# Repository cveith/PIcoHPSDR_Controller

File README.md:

# PIcoHPSDR Controller

A hardware controller for the piHPSDR application by John Melton, G0ORX.
I've called it PIcoHPSDR Controller, as it's using the newly released Raspberry Pi Pico as an abstraction layer to the hardware.

Inspired by the original controller and therefore parts of this work is based on the original PiHPSDR Controller designed by Kjell Karlsen, LA2NI, et al.
Many thanks Kjell.

## Features
- 1 VFO encoder (5V, open collector outputs)
- 4 Dual Shaft encoders (Alps EC11E type)
- 16 Push Buttons
- PTT, Up, Down, FST Scan from the MH31-A8J microphone
- External PTT, for foot switch
- CW Paddle input
- Audio Out via Headphone or Speaker Output
- Audio In via MH31-A8J Microphone from Yaesu

For more details on piHPSDR, please see https://github.com/g0orx/pihpsdr.

## Protocol Details
The data transmission protocol is pretty straight forward.
Each control element has it's own 7-bit address from Bit 1 through 7.
Bit 0 is reserved for the data portion.

Rotary encoder moves are indicated with value 0 for a counterclockwise step and 1 for a clockwise step.

### Example
PC receives 0b00000010 (Addr: 1, Data: 0):
The main VFO encoder has been turned ccw.

PC receives 0b00000100 (Addr: 2, Data: 1):
The encoder 2 has been turned clock wise.

PC receives 0b00010110 (Addr: 11, Data: 1):
The Encoder 2 Button has been pressed.

PC receives 0b00010110 (Addr: 11, Data: 0):
Encoder 2 Button has been released.

The release state is not used for most switches, but necessary for the external PTT and the Microphone PTT button.

The firmware is split of on a separate repository. Please see https://github.com/cveith/PIcoHPSDR_Controller_Firmware.
Detailed address informations are in a Openoffice Calc file as well.

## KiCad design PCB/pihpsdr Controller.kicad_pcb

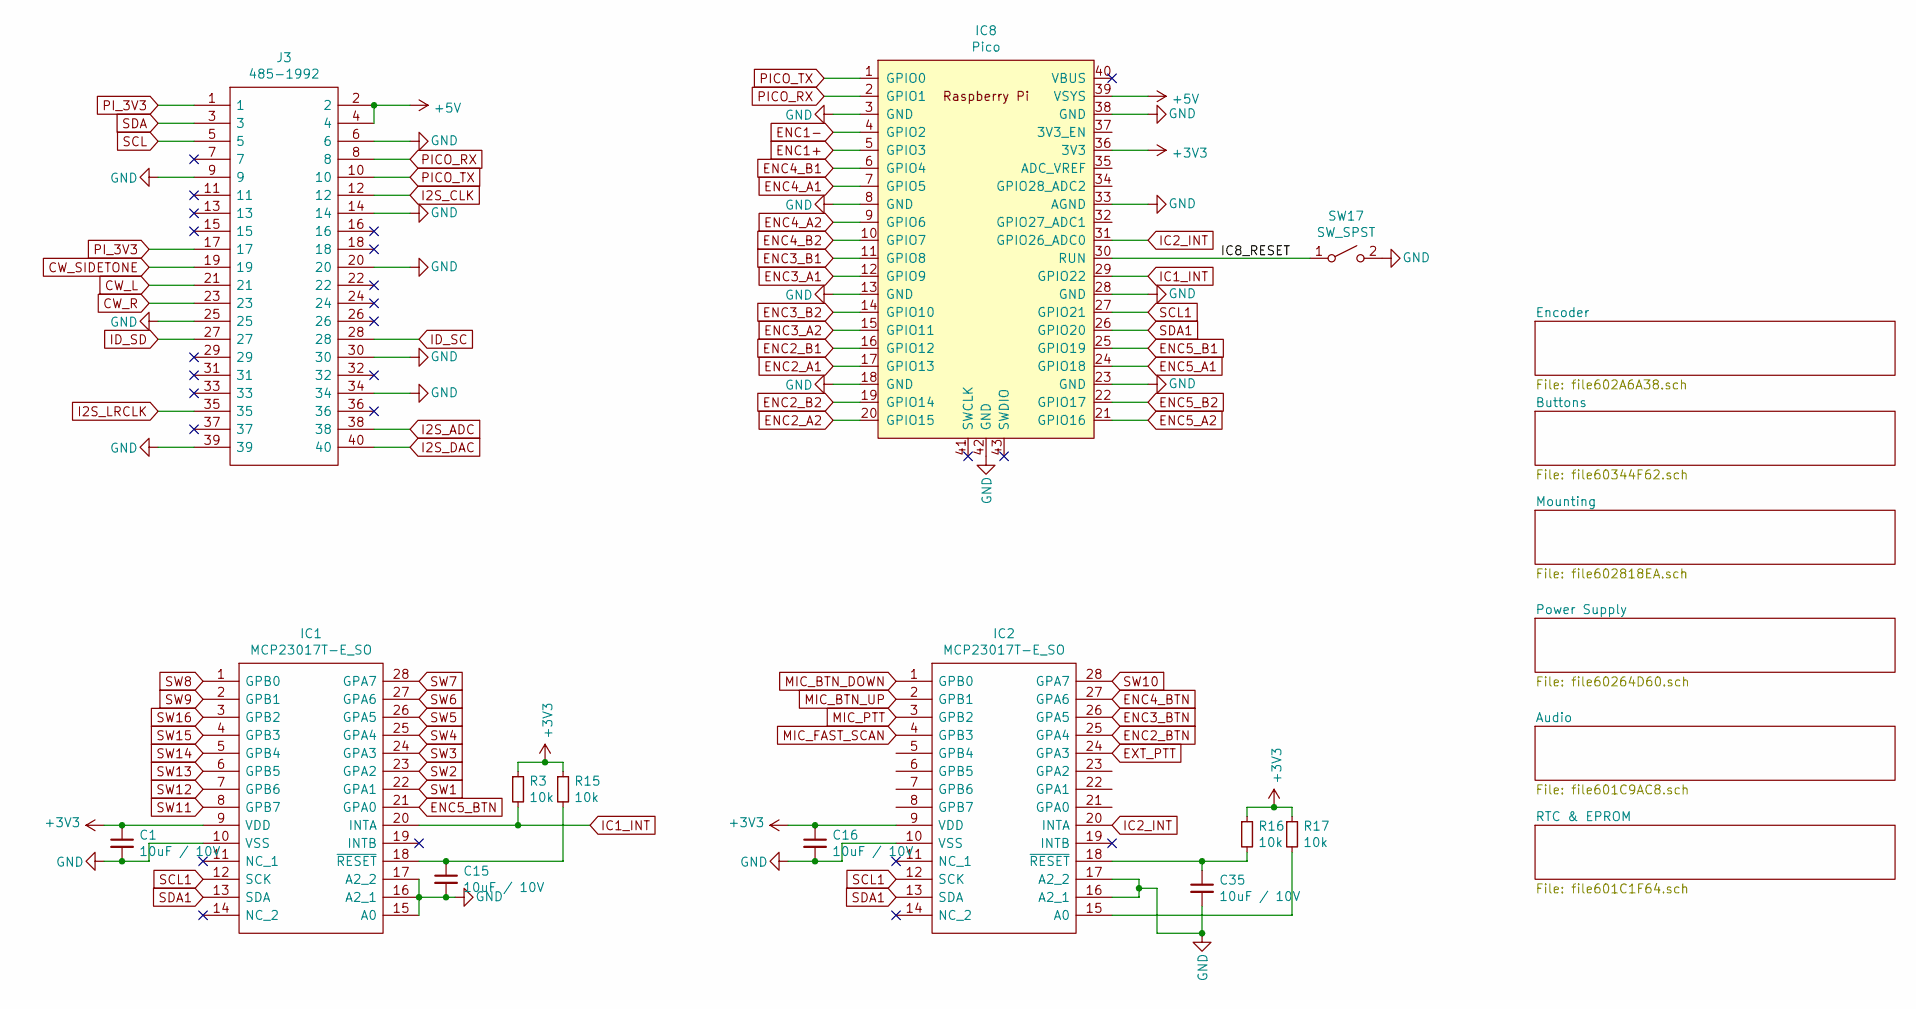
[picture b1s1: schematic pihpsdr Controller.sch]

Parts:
C1, C15, C16, C35: 10uF / 10V; C_0805_2012Metric_Pad1.15x1.40mm_HandSolder; Manufacturer_Part_Number CL21A106MPFNNNE; LCSC C15850
IC1, IC2: MCP23017T-E_SO; SOIC127P1030X265-28N; Mouser Part Number 579-MCP23017T-E/SO
IC8: Pico; RPi_Pico_SMD_TH; Mouser Part Number 474-DEV-17829
J3: 485-1992; 15445840_PI; Mouser Part Number 485-1992
R3: 10k; R_0805_2012Metric_Pad1.15x1.40mm_HandSolder; Mouser Part Number 71-CRCW080510K0FKEAC
R15, R16, R17: 10k; R_0805_2012Metric_Pad1.15x1.40mm_HandSolder; Manufacturer_Part_Number CRCW080510K0FKEAC; LCSC C17414
SW17: SW_SPST; TL3301SPF260QG; Manufacturer_Part_Number TL3301AF160QG; LCSC C273519

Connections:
+3V3: C1.1, C16.1, IC1.9 (VDD), IC2.9 (VDD), IC8.36 (3V3), R3.1, R15.1, R16.1, R17.1; also elsewhere on the board
+5V: IC8.39 (VSYS), J3.2, J3.4; also elsewhere on the board
/IC8_RESET: IC8.30 (RUN), SW17.1 (A)
CW_L: J3.21; also elsewhere on the board
CW_R: J3.23; also elsewhere on the board
CW_SIDETONE: J3.19; also elsewhere on the board
ENC1+: IC8.5 (GPIO3); also elsewhere on the board
ENC1-: IC8.4 (GPIO2); also elsewhere on the board
ENC2_A1: IC8.17 (GPIO13); also elsewhere on the board
ENC2_A2: IC8.20 (GPIO15); also elsewhere on the board
ENC2_B1: IC8.16 (GPIO12); also elsewhere on the board
ENC2_B2: IC8.19 (GPIO14); also elsewhere on the board
ENC2_BTN: IC2.25 (GPA4); also elsewhere on the board
ENC3_A1: IC8.12 (GPIO9); also elsewhere on the board
ENC3_A2: IC8.15 (GPIO11); also elsewhere on the board
ENC3_B1: IC8.11 (GPIO8); also elsewhere on the board
ENC3_B2: IC8.14 (GPIO10); also elsewhere on the board
ENC3_BTN: IC2.26 (GPA5); also elsewhere on the board
ENC4_A1: IC8.7 (GPIO5); also elsewhere on the board
ENC4_A2: IC8.9 (GPIO6); also elsewhere on the board
ENC4_B1: IC8.6 (GPIO4); also elsewhere on the board
ENC4_B2: IC8.10 (GPIO7); also elsewhere on the board
ENC4_BTN: IC2.27 (GPA6); also elsewhere on the board
ENC5_A1: IC8.24 (GPIO18); also elsewhere on the board
ENC5_A2: IC8.21 (GPIO16); also elsewhere on the board
ENC5_B1: IC8.25 (GPIO19); also elsewhere on the board
ENC5_B2: IC8.22 (GPIO17); also elsewhere on the board
ENC5_BTN: IC1.21 (GPA0); also elsewhere on the board
EXT_PTT: IC2.24 (GPA3); also elsewhere on the board
GND: C1.2, C15.2, C16.2, C35.2, IC1.10 (VSS), IC1.15 (A0), IC1.16 (A2_1), IC1.17 (A2_2), IC2.10 (VSS), IC2.16 (A2_1), IC2.17 (A2_2), IC8.3 (GND), IC8.8 (GND), IC8.13 (GND), IC8.18 (GND), IC8.23 (GND), IC8.28 (GND), IC8.33 (AGND), IC8.38 (GND), IC8.42 (GND), J3.6, J3.9, J3.14, J3.20, J3.25, J3.30, J3.34, J3.39, SW17.2 (B); also elsewhere on the board
I2S_ADC: J3.38; also elsewhere on the board
I2S_CLK: J3.12; also elsewhere on the board
I2S_DAC: J3.40; also elsewhere on the board
I2S_LRCLK: J3.35; also elsewhere on the board
IC1_INT: IC1.20 (INTA), IC8.29 (GPIO22), R3.2
IC2_INT: IC2.20 (INTA), IC8.31 (GPIO26_ADC0)
ID_SC: J3.28; also elsewhere on the board
ID_SD: J3.27; also elsewhere on the board
MIC_BTN_DOWN: IC2.1 (GPB0); also elsewhere on the board
MIC_BTN_UP: IC2.2 (GPB1); also elsewhere on the board
MIC_FAST_SCAN: IC2.4 (GPB3); also elsewhere on the board
MIC_PTT: IC2.3 (GPB2); also elsewhere on the board
unnamed: C15.1, IC1.18 (~RESET), R15.2
unnamed: C35.1, IC2.18 (~RESET), R16.2
unnamed: IC2.15 (A0), R17.2
PICO_RX: IC8.2 (GPIO1), J3.8
PICO_TX: IC8.1 (GPIO0), J3.10
PI_3V3: J3.1, J3.17; also elsewhere on the board
SCL: J3.5; also elsewhere on the board
SCL1: IC1.12 (SCK), IC2.12 (SCK), IC8.27 (GPIO21)
SDA: J3.3; also elsewhere on the board
SDA1: IC1.13 (SDA), IC2.13 (SDA), IC8.26 (GPIO20)
SW1: IC1.22 (GPA1); also elsewhere on the board
SW2: IC1.23 (GPA2); also elsewhere on the board
SW3: IC1.24 (GPA3); also elsewhere on the board
SW4: IC1.25 (GPA4); also elsewhere on the board
SW5: IC1.26 (GPA5); also elsewhere on the board
SW6: IC1.27 (GPA6); also elsewhere on the board
SW7: IC1.28 (GPA7); also elsewhere on the board
SW8: IC1.1 (GPB0); also elsewhere on the board
SW9: IC1.2 (GPB1); also elsewhere on the board
SW10: IC2.28 (GPA7); also elsewhere on the board
SW11: IC1.8 (GPB7); also elsewhere on the board
SW12: IC1.7 (GPB6); also elsewhere on the board
SW13: IC1.6 (GPB5); also elsewhere on the board
SW14: IC1.5 (GPB4); also elsewhere on the board
SW15: IC1.4 (GPB3); also elsewhere on the board
SW16: IC1.3 (GPB2); also elsewhere on the board

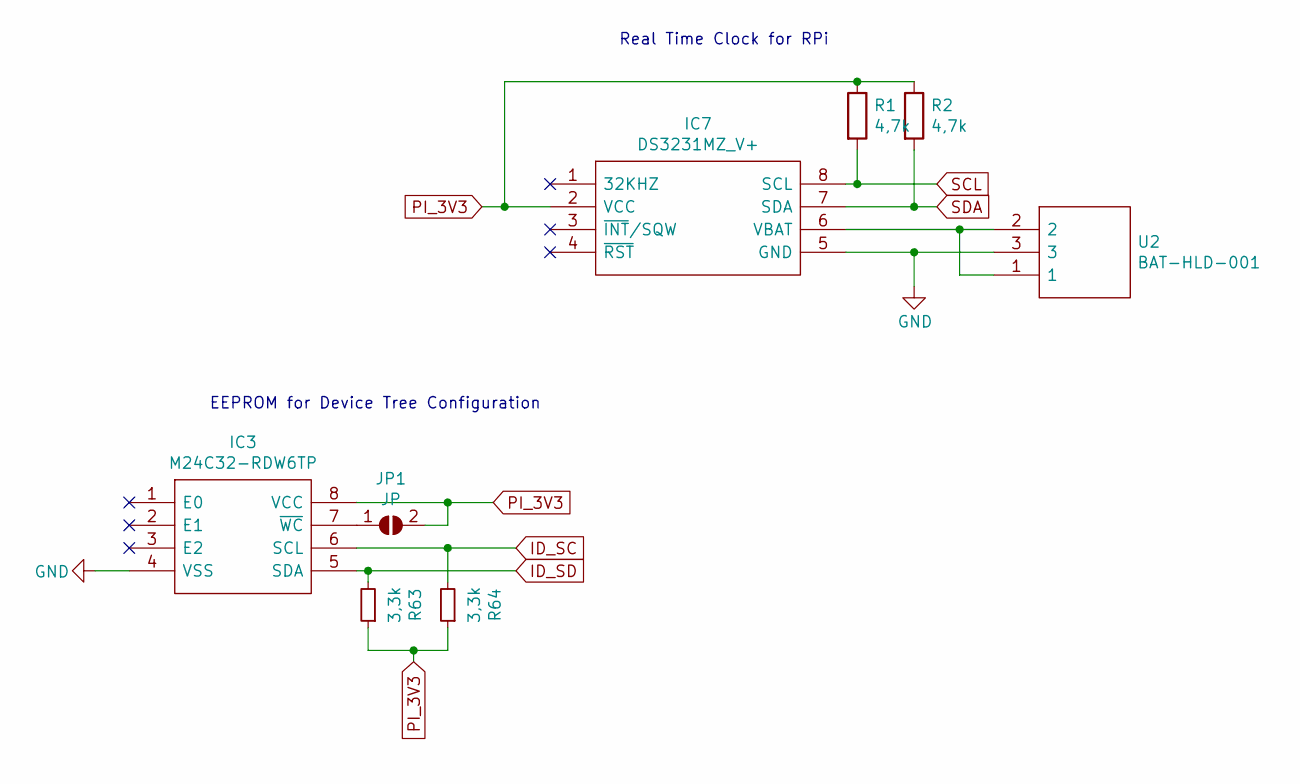
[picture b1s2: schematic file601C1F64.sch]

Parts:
IC3: M24C32-RDW6TP; SOP65P640X120-8N; Mouser Part Number 511-M24C32-RDW6TP
IC7: DS3231MZ_V+; SOIC127P600X175-8N; Mouser Part Number 700-DS3231MZ/V+
JP1: JP; SolderJumper-2_P1.3mm_Open_RoundedPad1.0x1.5mm
R1, R2: 4,7k; R_0805_2012Metric_Pad1.15x1.40mm_HandSolder; Manufacturer_Part_Number CRCW08054K70FKEAC; LCSC C17673
R63, R64: 3,3k; R_0805_2012Metric_Pad1.15x1.40mm_HandSolder; Manufacturer_Part_Number CRCW08053K30FKEAC; LCSC C26010
U2: BAT-HLD-001; BATHLD001; Mouser Part Number 712-BAT-HLD-001

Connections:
GND: IC3.4 (VSS), IC7.5 (GND), U2.3; also elsewhere on the board
ID_SC: IC3.6 (SCL), R64.2; also elsewhere on the board
ID_SD: IC3.5 (SDA), R63.2; also elsewhere on the board
unnamed: IC3.7 (~WC), JP1.1 (A)
unnamed: IC7.6 (VBAT), U2.1, U2.2
PI_3V3: IC3.8 (VCC), IC7.2 (VCC), JP1.2 (B), R1.1, R2.1, R63.1, R64.1; also elsewhere on the board
SCL: IC7.8 (SCL), R1.2; also elsewhere on the board
SDA: IC7.7 (SDA), R2.2; also elsewhere on the board

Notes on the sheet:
EEPROM for Device Tree Configuration
Real Time Clock for RPi

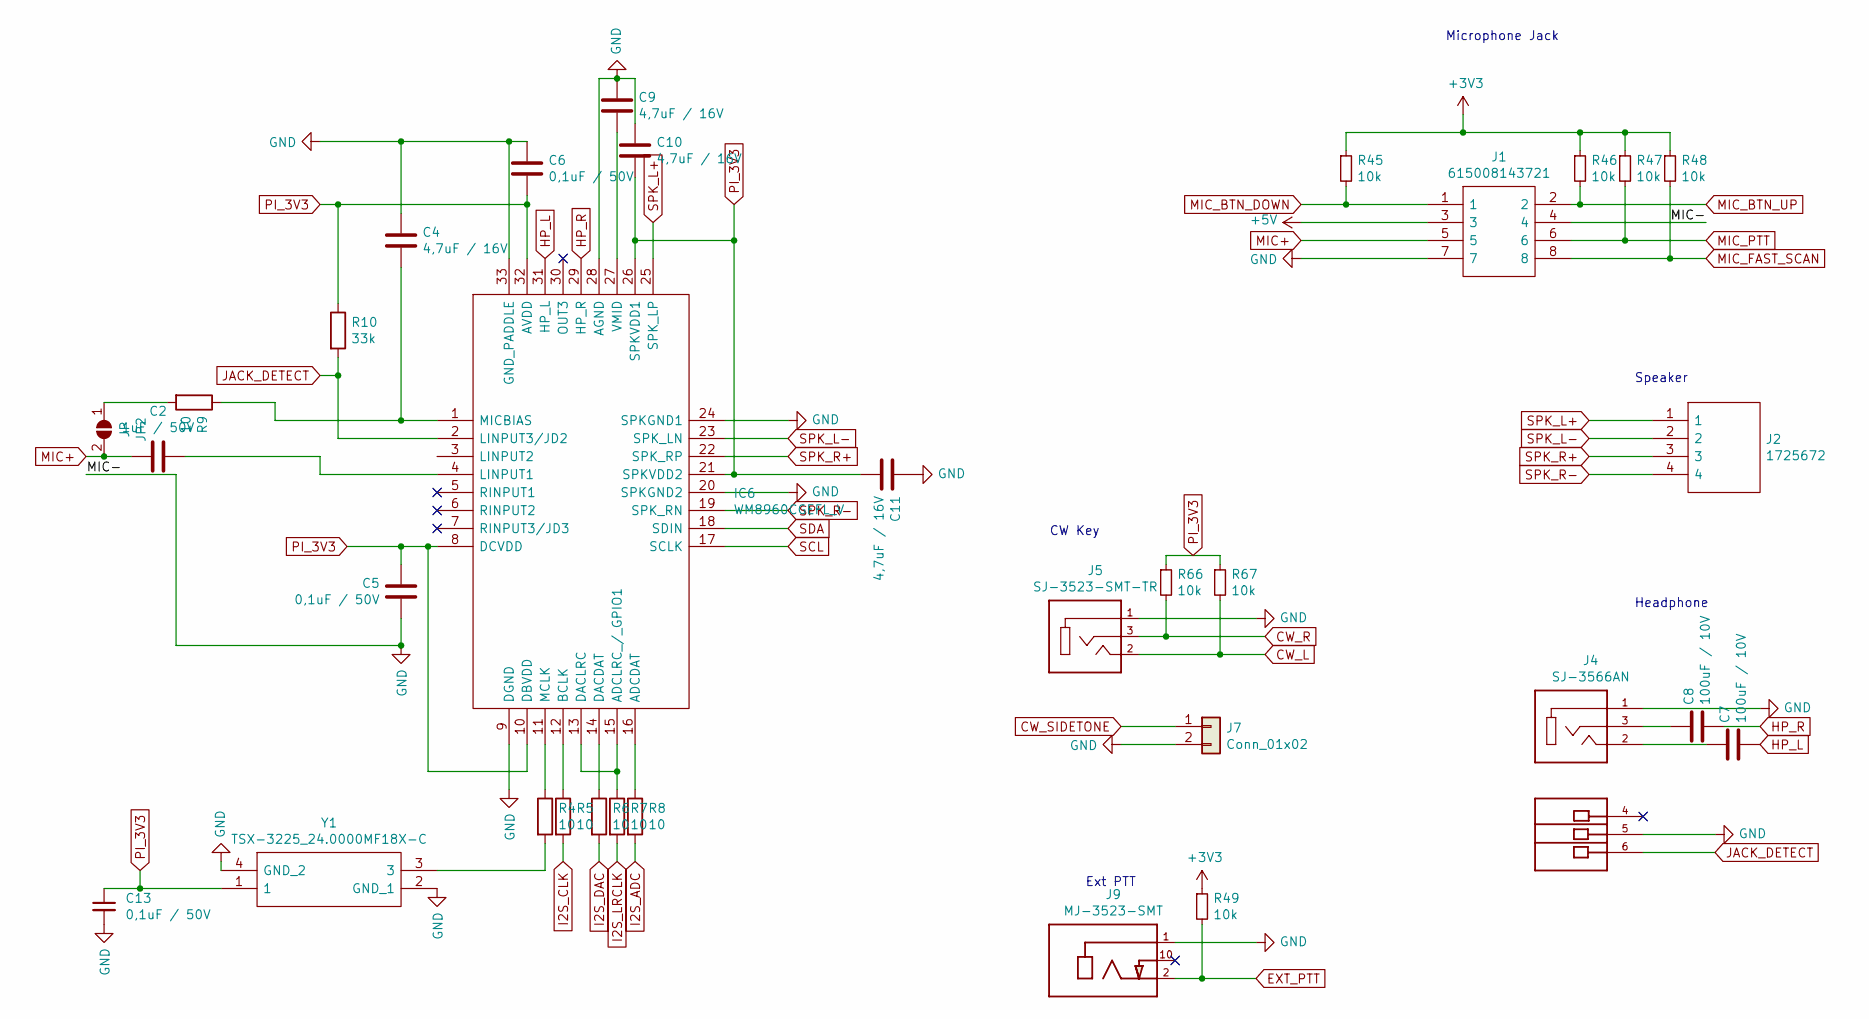
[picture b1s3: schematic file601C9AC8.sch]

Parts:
C2: 1uF / 50V; C_0805_2012Metric_Pad1.15x1.40mm_HandSolder; Manufacturer_Part_Number CL21B105KBFNNNE; LCSC C28323
C4, C9, C10, C11: 4,7uF / 16V; C_0805_2012Metric_Pad1.15x1.40mm_HandSolder; Manufacturer_Part_Number CL21A475KOFNNNE; LCSC C1779
C5, C6, C13: 0,1uF / 50V; C_0805_2012Metric_Pad1.15x1.40mm_HandSolder; Manufacturer_Part_Number CL21B104KBCSFNC; LCSC C49678
C7, C8: 100uF / 10V; C_1206_3216Metric_Pad1.42x1.75mm_HandSolder; Manufacturer_Part_Number GRM32ER61A107ME20L; LCSC C84455
IC6: WM8960CGEFL_V; CUST_QFN-32-1EP_5x5mm_P0.5mm_EP3.45x3.45mm; Mouser Part Number 238-WM8960CGEFL/V
J1: 615008143721; Mouser Part Number 710-615008143721
J2: 1725672; 1725672-4-2.54; Mouser Part Number 651-1725672
J4: SJ-3566AN; CUI_SJ-3566AN; Manufacturer_Part_Number SJ-3566AN; Mouser Part Number 490-SJ-3566AN
J5: SJ-3523-SMT-TR; CUI_SJ-3523-SMT-TR; Manufacturer_Part_Number SJ-3523-SMT-TR; Mouser Part Number 490-SJ-3523-SMT-TR
J7: Conn_01x02; PinHeader_1x02_P2.54mm_Horizontal; Manufacturer_Part_Number 10129379-902001BLF; Mouser Part Number 649-1012937990201BLF
J9: MJ-3523-SMT; CUI_MJ-3523-SMT; PART_REV D; Mouser Part Number 490-MJ-3523-SMT-TR
JP2: JP; SolderJumper-2_P1.3mm_Open_RoundedPad1.0x1.5mm
R4, R5, R6, R7, R8, R9: 10; R_0805_2012Metric_Pad1.15x1.40mm_HandSolder; Manufacturer_Part_Number CRCW080510R0FKEB; LCSC C17415
R10: 33k; R_0805_2012Metric_Pad1.15x1.40mm_HandSolder; Manufacturer_Part_Number CRCW080533K0FKEA; LCSC C17633
R45, R46, R47, R48, R49, R66, R67: 10k; R_0805_2012Metric_Pad1.15x1.40mm_HandSolder; Manufacturer_Part_Number CRCW080510K0FKEAC; LCSC C17414
Y1: TSX-3225_24.0000MF18X-C; TSX3225160000MF18XAC0; Mouser Part Number 732-TSX-32224MF18X-C

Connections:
+3V3: R45.1, R46.1, R47.1, R48.1, R49.1; also elsewhere on the board
+5V: J1.3; also elsewhere on the board
CW_L: J5.2, R67.2; also elsewhere on the board
CW_R: J5.3, R66.2; also elsewhere on the board
CW_SIDETONE: J7.1; also elsewhere on the board
EXT_PTT: J9.2, R49.2; also elsewhere on the board
GND: C4.1, C5.2, C6.1, C9.1, C10.1, C11.1, C13.2, IC6.9 (DGND), IC6.20 (SPKGND2), IC6.24 (SPKGND1), IC6.28 (AGND), IC6.33 (GND_PADDLE), J1.4, J1.7, J4.1, J4.5, J5.1, J7.2, J9.1, Y1.2 (GND_1), Y1.4 (GND_2); also elsewhere on the board
HP_L: C7.2, IC6.31 (HP_L)
HP_R: C8.2, IC6.29 (HP_R)
I2S_ADC: R8.2; also elsewhere on the board
I2S_CLK: R5.2; also elsewhere on the board
I2S_DAC: R6.2; also elsewhere on the board
I2S_LRCLK: R7.2; also elsewhere on the board
JACK_DETECT: IC6.2 (LINPUT3/JD2), J4.6, R10.2
MIC+: C2.1, J1.5, JP2.2 (B)
MIC_BTN_DOWN: J1.1, R45.2; also elsewhere on the board
MIC_BTN_UP: J1.2, R46.2; also elsewhere on the board
MIC_FAST_SCAN: J1.8, R48.2; also elsewhere on the board
MIC_PTT: J1.6, R47.2; also elsewhere on the board
unnamed: C2.2, IC6.4 (LINPUT1)
unnamed: C4.2, IC6.1 (MICBIAS), R9.1
unnamed: C7.1, J4.2
unnamed: C8.1, J4.3
unnamed: C9.2, IC6.27 (VMID)
unnamed: IC6.11 (MCLK), R4.1
unnamed: IC6.12 (BCLK), R5.1
unnamed: IC6.13 (DACLRC), IC6.15 (ADCLRC_/_GPIO1), R7.1
unnamed: IC6.14 (DACDAT), R6.1
unnamed: IC6.16 (ADCDAT), R8.1
unnamed: JP2.1 (A), R9.2
unnamed: R4.2, Y1.3
PI_3V3: C5.1, C6.2, C10.2, C11.2, C13.1, IC6.8 (DCVDD), IC6.10 (DBVDD), IC6.21 (SPKVDD2), IC6.26 (SPKVDD1), IC6.32 (AVDD), R10.1, R66.1, R67.1, Y1.1; also elsewhere on the board
SCL: IC6.17 (SCLK); also elsewhere on the board
SDA: IC6.18 (SDIN); also elsewhere on the board
SPK_L+: IC6.25 (SPK_LP), J2.1
SPK_L-: IC6.23 (SPK_LN), J2.2
SPK_R+: IC6.22 (SPK_RP), J2.3
SPK_R-: IC6.19 (SPK_RN), J2.4

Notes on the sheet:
Headphone
Speaker
Microphone Jack
Ext PTT
CW Key

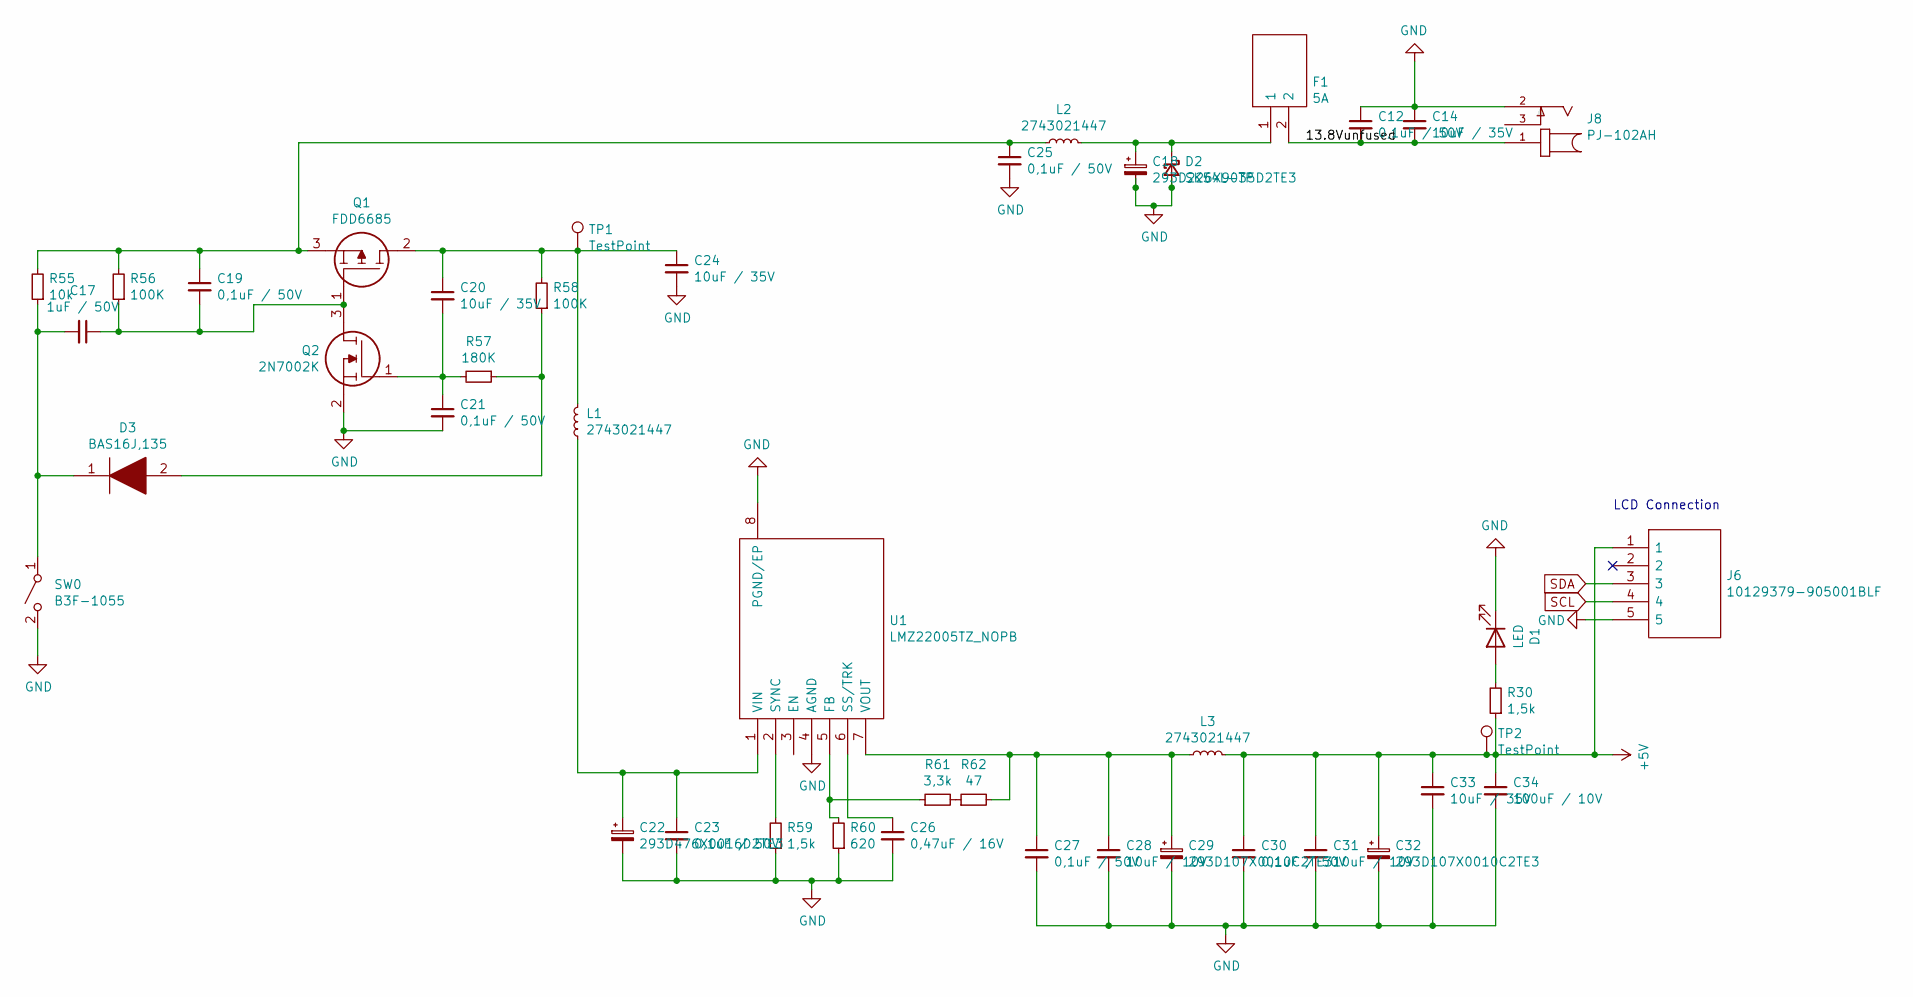
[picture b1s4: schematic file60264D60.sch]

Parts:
C12, C19, C21, C23, C25, C27, C30: 0,1uF / 50V; C_0805_2012Metric_Pad1.15x1.40mm_HandSolder; Manufacturer_Part_Number CL21B104KBCSFNC; LCSC C49678
C14, C20, C24, C33: 10uF / 35V; C_0805_2012Metric_Pad1.15x1.40mm_HandSolder; Manufacturer_Part_Number CL21A106KAYNNNE; Mouser Part Number 187-CL21A106KAYNNNE
C17: 1uF / 50V; C_0805_2012Metric_Pad1.15x1.40mm_HandSolder; Manufacturer_Part_Number CL21B105KBFNNNE; LCSC C28323
C18: 293D226X9035D2TE3; CAPPM7343X310N; Mouser Part Number 74-293D226X9035D2TE3
C22: 293D476X0016D2TE3; CAPPM7343X310N; Mouser Part Number 74-293D476X0016D2TE3
C26: 0,47uF / 16V; C_0805_2012Metric_Pad1.15x1.40mm_HandSolder; Manufacturer_Part_Number CL21B474KBFNNNE; Mouser Part Number 187-CL21B474KBFNNNE
C28, C31: 10uF / 10V; C_0805_2012Metric_Pad1.15x1.40mm_HandSolder; Manufacturer_Part_Number CL21A106MPFNNNE; LCSC C15850
C29, C32: 293D107X0010C2TE3; CAPPM6032X280N; Mouser Part Number 74-293D107X0010C2TE3
C34: 100uF / 10V; C_1206_3216Metric_Pad1.42x1.75mm_HandSolder; Manufacturer_Part_Number GRM32ER61A107ME20L; LCSC C84455
D1: LED; LED_D5.0mm
D2: SK54L-TP; DIOM7959X262N; Mouser Part Number 833-SK54L-TP
D3: BAS16J,135; SODFL2512X80N; Mouser Part Number 771-BAS16J135
F1: 5A; 65600001009; Mouser Part Number 576-65600001009
J6: 10129379-905001BLF; HDRRA5W67P0X254_1X5_1270X254X241P; Mouser Part Number 649-1012937990501BLF
J8: PJ-102AH; CUI_PJ-102AH; PART_REV 1.02; Mouser Part Number 490-PJ-102AH
L1, L2, L3: 2743021447; Mouser Part Number 623-2743021447LF
Q1: FDD6685; FQD1N80TM; Mouser Part Number 512-FDD6685
Q2: 2N7002K; SOT95P240X120-3N; Mouser Part Number 512-2N7002K
R30, R59: 1,5k; R_0805_2012Metric_Pad1.15x1.40mm_HandSolder; Manufacturer_Part_Number CRCW08051K50FKEA; LCSC C4310
R55: 10k; R_0805_2012Metric_Pad1.15x1.40mm_HandSolder; Manufacturer_Part_Number CRCW080510K0FKEAC; LCSC C17414
R56, R58: 100K; R_0805_2012Metric_Pad1.15x1.40mm_HandSolder; Manufacturer_Part_Number CRCW0805100KFKEAC; LCSC C17407
R57: 180K; R_0805_2012Metric_Pad1.15x1.40mm_HandSolder; Manufacturer_Part_Number CRCW0805180KFKEAC; LCSC C17501
R60: 620; R_0805_2012Metric_Pad1.15x1.40mm_HandSolder; Manufacturer_Part_Number CRCW0805620RFKEA; LCSC C23220
R61: 3,3k; R_0805_2012Metric_Pad1.15x1.40mm_HandSolder; Manufacturer_Part_Number CRCW08053K30FKEAC; LCSC C26010
R62: 47; R_0805_2012Metric_Pad1.15x1.40mm_HandSolder; Manufacturer_Part_Number CRCW080547R0FKEAC; LCSC C17714
SW0: B3F-1055; B3F1000; Mouser Part Number 653-B3F-1055
TP1, TP2: TestPoint; TestPoint_Pad_D3.0mm
U1: LMZ22005TZ_NOPB; NDW0007A; Mouser Part Number 926-LMZ22005TZ/NOPB

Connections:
+5V: C30.1, C31.1, C32.1, C33.1, C34.1, J6.1, L3.2, R30.1, TP2.1; also elsewhere on the board
/Power Supply/13.8Vunfused: C12.2, C14.2, F1.2, J8.1
GND: C12.1, C14.1, C18.2, C21.2, C22.2, C23.2, C24.2, C25.2, C26.2, C27.2, C28.2, C29.2, C30.2, C31.2, C32.2, C33.2, C34.2, D1.1 (K), D2.2 (A), J6.5, J8.2, Q2.2, R59.1, R60.1, SW0.2 (B), U1.4 (AGND), U1.8 (PGND/EP); also elsewhere on the board
unnamed: C17.1, C19.2, Q1.1, Q2.3, R56.1
unnamed: C17.2, D3.1, R55.1, SW0.1 (A)
unnamed: C18.1, D2.1 (K), F1.1, L2.2
unnamed: C19.1, C25.1, L2.1, Q1.3, R55.2, R56.2
unnamed: C20.1, C24.1, L1.2, Q1.2, R58.2, TP1.1
unnamed: C20.2, C21.1, Q2.1, R57.2
unnamed: C22.1, C23.1, L1.1, U1.1 (VIN)
unnamed: C26.1, U1.6 (SS/TRK)
unnamed: C27.1, C28.1, C29.1, L3.1, R62.2, U1.7 (VOUT)
unnamed: D1.2 (A), R30.2
unnamed: D3.2, R57.1, R58.1
unnamed: R59.2, U1.2 (SYNC)
unnamed: R60.2, R61.1, U1.5 (FB)
unnamed: R61.2, R62.1
SCL: J6.4; also elsewhere on the board
SDA: J6.3; also elsewhere on the board

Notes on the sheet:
LCD Connection

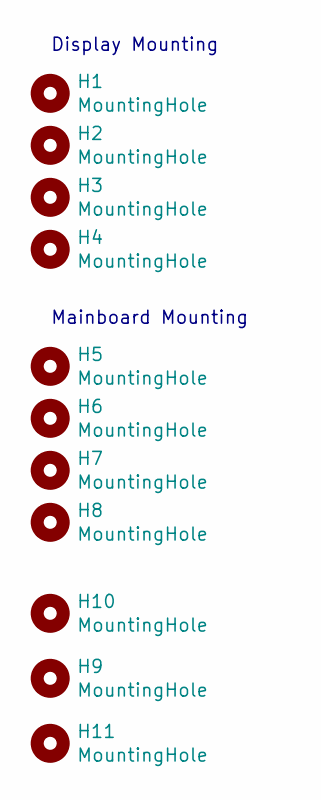
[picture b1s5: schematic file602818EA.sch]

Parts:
H1, H2, H3, H4: MountingHole; MountingHole_3.5mm_Pad
H5, H6, H7, H8, H9, H10, H11: MountingHole; MountingHole_3.2mm_M3_DIN965_Pad

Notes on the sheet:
Mainboard Mounting
Display Mounting

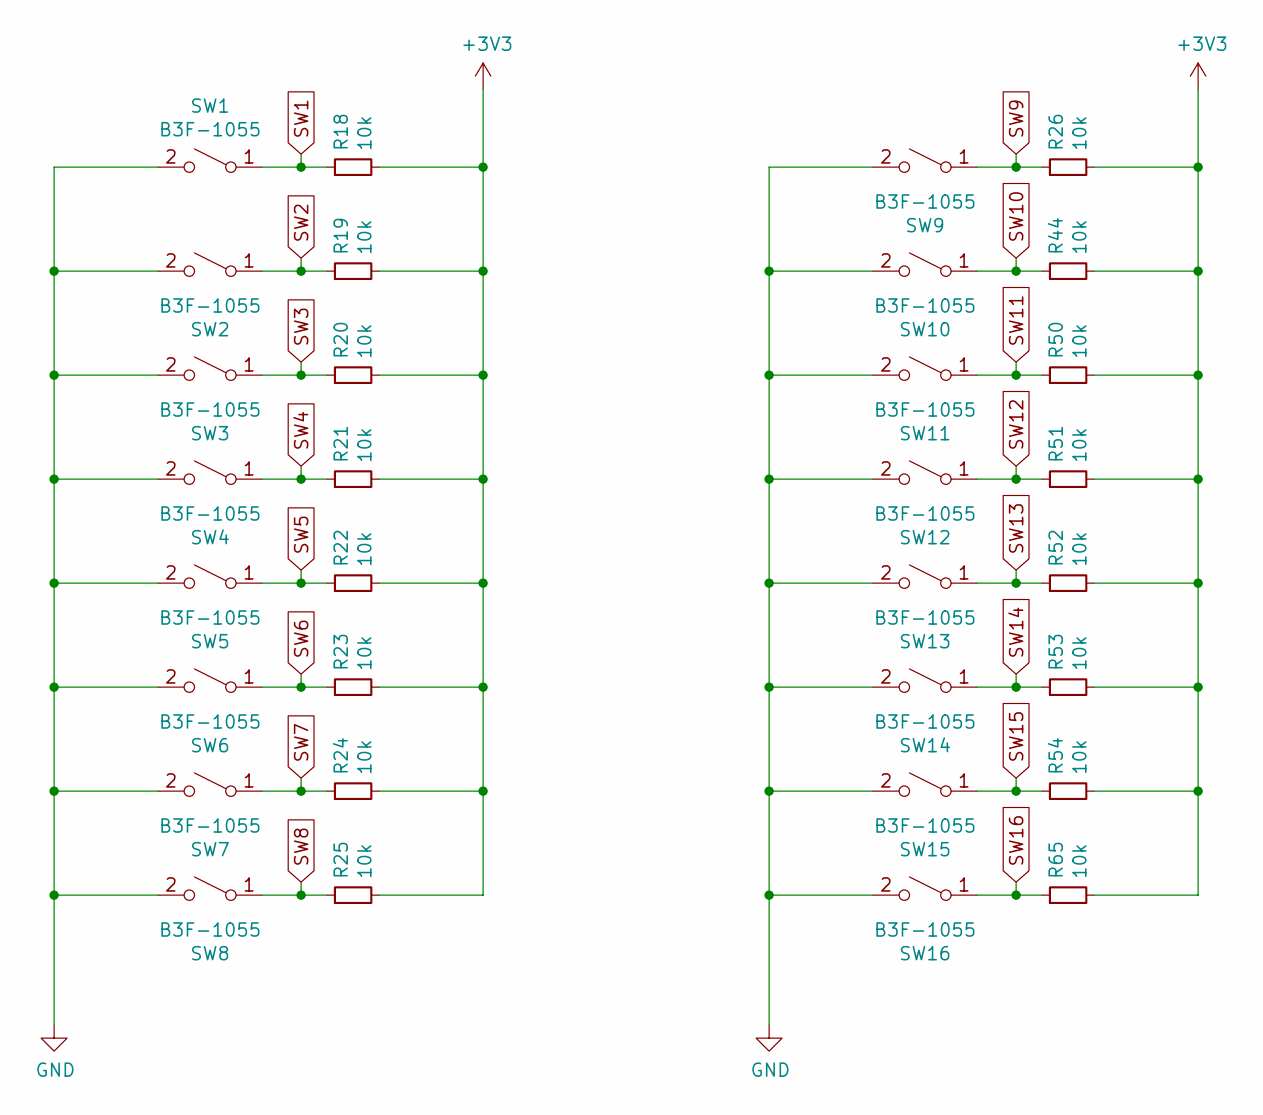
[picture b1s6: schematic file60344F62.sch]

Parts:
R18, R19, R20, R21, R22, R23, R24, R25, R26, R44, R50, R51, R52, R53, R54, R65: 10k; R_0805_2012Metric_Pad1.15x1.40mm_HandSolder; Manufacturer_Part_Number CRCW080510K0FKEAC; LCSC C17414
SW1, SW2, SW3, SW4, SW5, SW6, SW7, SW8, SW9, SW10, SW11, SW12, SW13, SW14, SW15, SW16: B3F-1055; B3F1000; Mouser Part Number 653-B3F-1055

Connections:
+3V3: R18.2, R19.2, R20.2, R21.2, R22.2, R23.2, R24.2, R25.2, R26.2, R44.2, R50.2, R51.2, R52.2, R53.2, R54.2, R65.2; also elsewhere on the board
GND: SW1.2 (B), SW2.2 (B), SW3.2 (B), SW4.2 (B), SW5.2 (B), SW6.2 (B), SW7.2 (B), SW8.2 (B), SW9.2 (B), SW10.2 (B), SW11.2 (B), SW12.2 (B), SW13.2 (B), SW14.2 (B), SW15.2 (B), SW16.2 (B); also elsewhere on the board
SW1: R18.1, SW1.1 (A); also elsewhere on the board
SW2: R19.1, SW2.1 (A); also elsewhere on the board
SW3: R20.1, SW3.1 (A); also elsewhere on the board
SW4: R21.1, SW4.1 (A); also elsewhere on the board
SW5: R22.1, SW5.1 (A); also elsewhere on the board
SW6: R23.1, SW6.1 (A); also elsewhere on the board
SW7: R24.1, SW7.1 (A); also elsewhere on the board
SW8: R25.1, SW8.1 (A); also elsewhere on the board
SW9: R26.1, SW9.1 (A); also elsewhere on the board
SW10: R44.1, SW10.1 (A); also elsewhere on the board
SW11: R50.1, SW11.1 (A); also elsewhere on the board
SW12: R51.1, SW12.1 (A); also elsewhere on the board
SW13: R52.1, SW13.1 (A); also elsewhere on the board
SW14: R53.1, SW14.1 (A); also elsewhere on the board
SW15: R54.1, SW15.1 (A); also elsewhere on the board
SW16: R65.1, SW16.1 (A); also elsewhere on the board

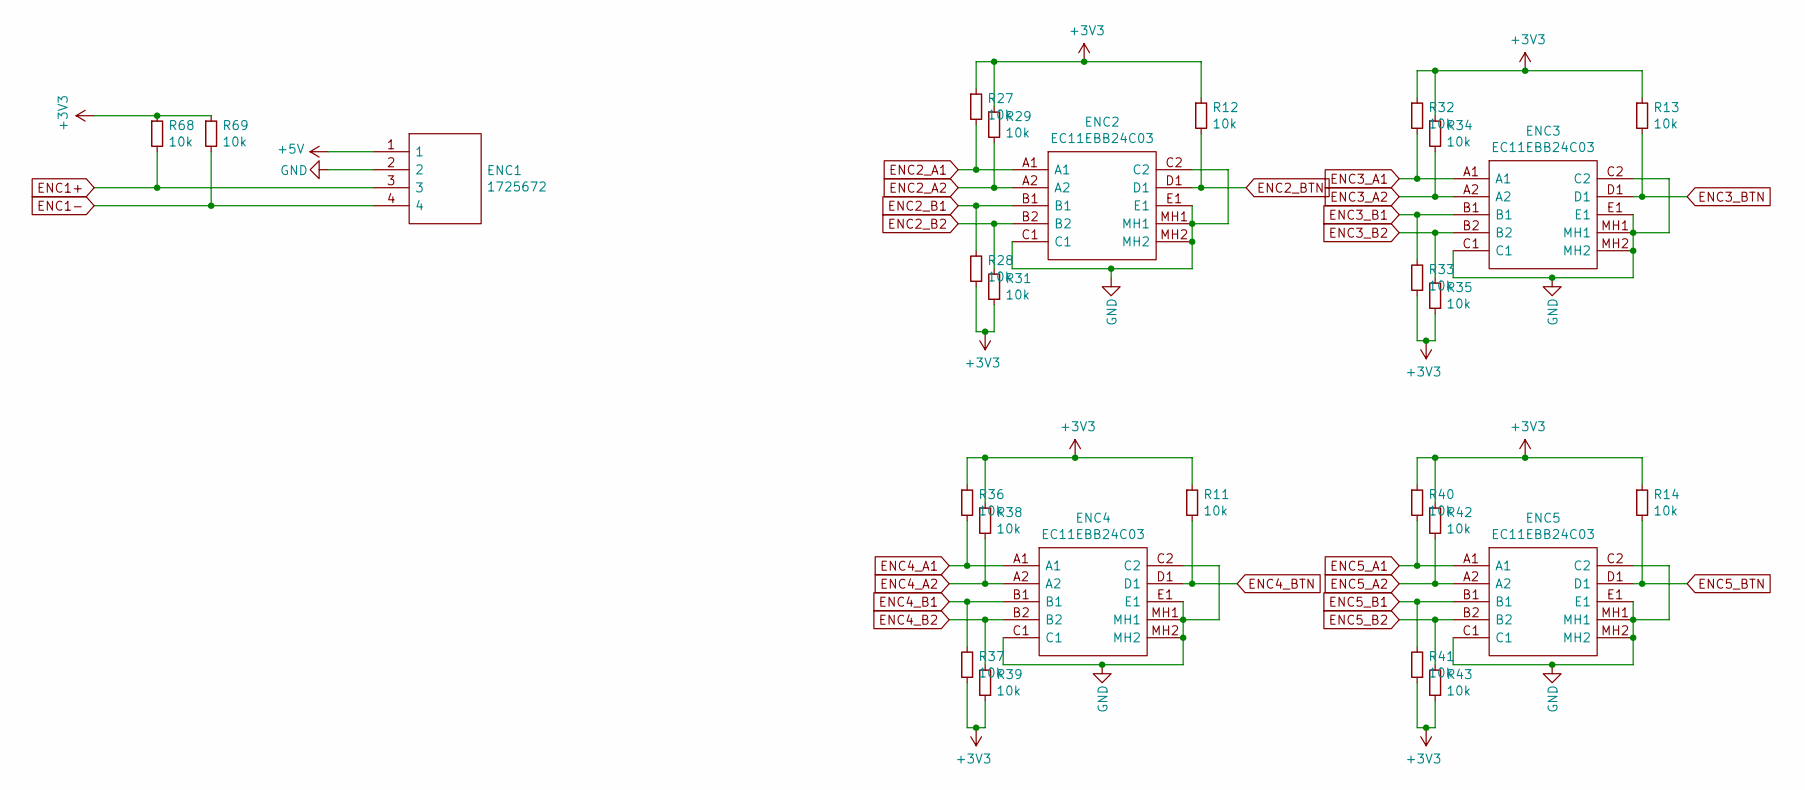
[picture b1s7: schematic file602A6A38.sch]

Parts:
ENC1: 1725672; 1725672-4-2.54; Mouser Part Number 651-1725672
ENC2, ENC3, ENC4, ENC5: EC11EBB24C03; Mouser Part Number 688-EC11EBB24C03
R11, R12, R13, R14, R27, R28, R29, R31, R32, R33, R34, R35, R36, R37, R38, R39, R40, R41, R42, R43, R68, R69: 10k; R_0805_2012Metric_Pad1.15x1.40mm_HandSolder; Manufacturer_Part_Number CRCW080510K0FKEAC; LCSC C17414

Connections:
+3V3: R11.1, R12.1, R13.1, R14.1, R27.1, R28.1, R29.1, R31.1, R32.1, R33.1, R34.1, R35.1, R36.1, R37.1, R38.1, R39.1, R40.1, R41.1, R42.1, R43.1, R68.1, R69.1; also elsewhere on the board
+5V: ENC1.1; also elsewhere on the board
ENC1+: ENC1.3, R68.2; also elsewhere on the board
ENC1-: ENC1.4, R69.2; also elsewhere on the board
ENC2_A1: ENC2.A1, R27.2; also elsewhere on the board
ENC2_A2: ENC2.A2, R29.2; also elsewhere on the board
ENC2_B1: ENC2.B1, R28.2; also elsewhere on the board
ENC2_B2: ENC2.B2, R31.2; also elsewhere on the board
ENC2_BTN: ENC2.D1, R12.2; also elsewhere on the board
ENC3_A1: ENC3.A1, R32.2; also elsewhere on the board
ENC3_A2: ENC3.A2, R34.2; also elsewhere on the board
ENC3_B1: ENC3.B1, R33.2; also elsewhere on the board
ENC3_B2: ENC3.B2, R35.2; also elsewhere on the board
ENC3_BTN: ENC3.D1, R13.2; also elsewhere on the board
ENC4_A1: ENC4.A1, R36.2; also elsewhere on the board
ENC4_A2: ENC4.A2, R38.2; also elsewhere on the board
ENC4_B1: ENC4.B1, R37.2; also elsewhere on the board
ENC4_B2: ENC4.B2, R39.2; also elsewhere on the board
ENC4_BTN: ENC4.D1, R11.2; also elsewhere on the board
ENC5_A1: ENC5.A1, R40.2; also elsewhere on the board
ENC5_A2: ENC5.A2, R42.2; also elsewhere on the board
ENC5_B1: ENC5.B1, R41.2; also elsewhere on the board
ENC5_B2: ENC5.B2, R43.2; also elsewhere on the board
ENC5_BTN: ENC5.D1, R14.2; also elsewhere on the board
GND: ENC1.2, ENC2.C1, ENC2.C2, ENC2.E1, ENC2.MH1, ENC2.MH2, ENC3.C1, ENC3.C2, ENC3.E1, ENC3.MH1, ENC3.MH2, ENC4.C1, ENC4.C2, ENC4.E1, ENC4.MH1, ENC4.MH2, ENC5.C1, ENC5.C2, ENC5.E1, ENC5.MH1, ENC5.MH2; also elsewhere on the board

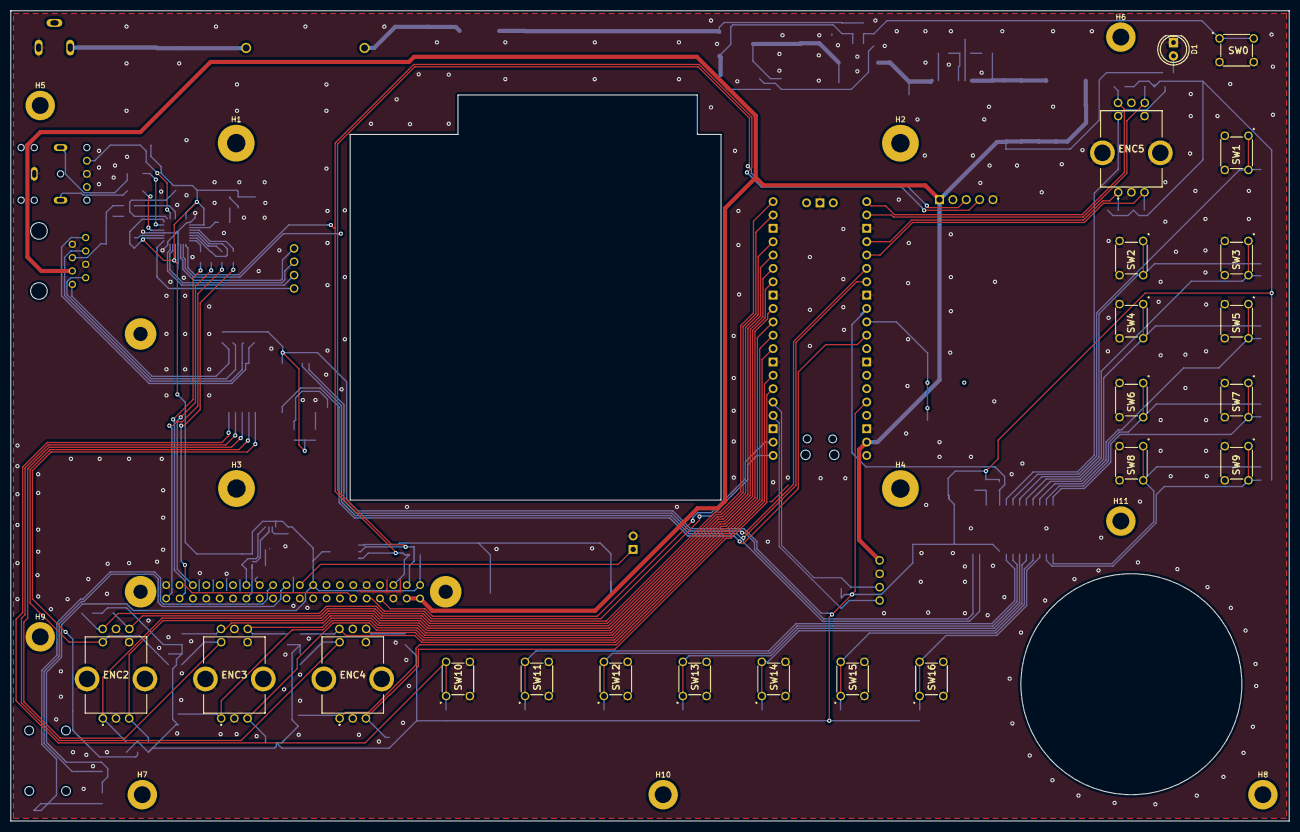
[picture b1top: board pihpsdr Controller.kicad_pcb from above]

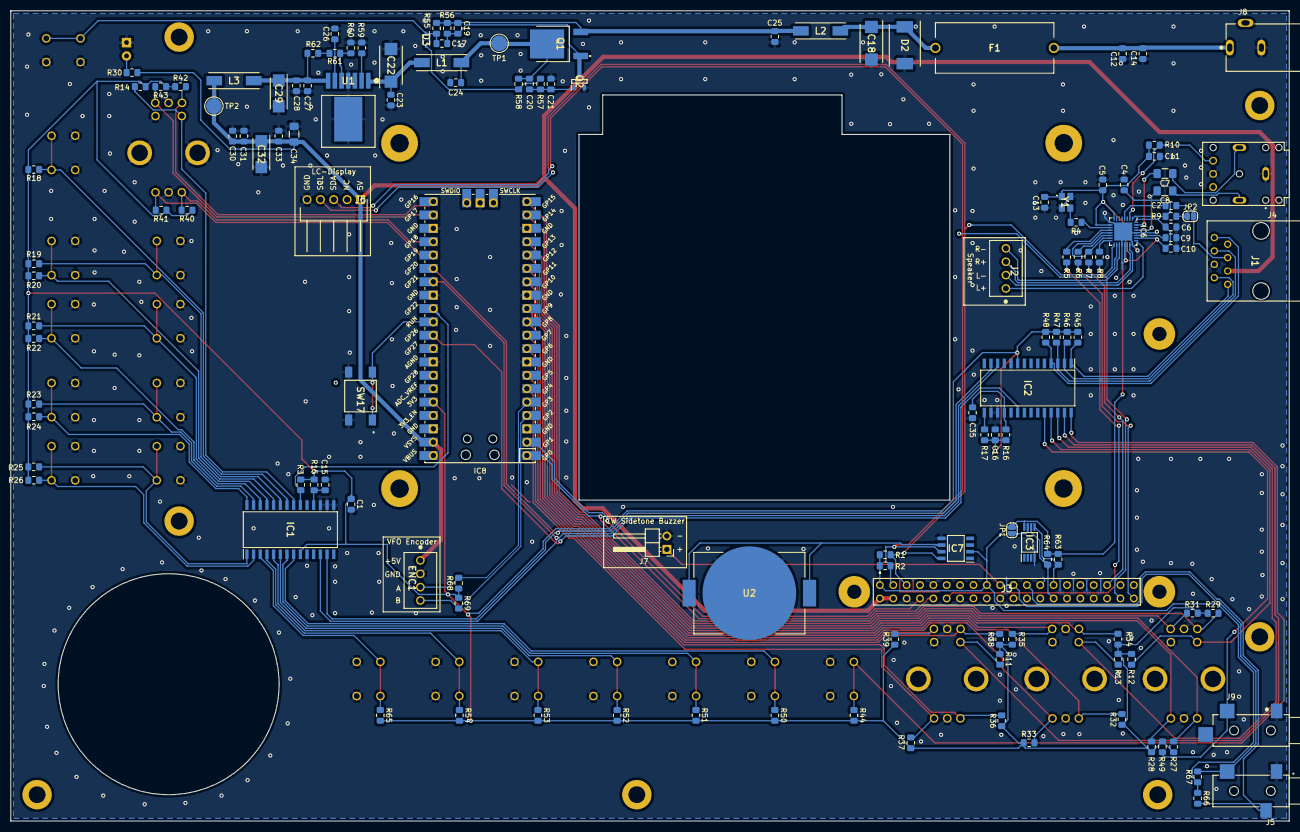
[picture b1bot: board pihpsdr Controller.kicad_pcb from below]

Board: 2 copper layers, 243.0 x 154.0 mm, 168 parts (135 on the bottom side), 105 nets.

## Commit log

2021-02-13 Inital checking. Still working on routing.
2021-02-13 Reorganized KiCad project
2021-02-17 Cleaned up repository. Created a BOM in iBOM Format.
2021-02-17 recreated BOM file.
2021-02-17 Added PDF Files for better readability without necessary tools.
2021-02-18 Completed parts details on schematics and recreated gerbers and bom.
2021-02-20 Replaced RMS20 encoder with Chinese encoder. Maybe a modification of the encoder is necessary due to internal 7805 voltage regulator.
2021-02-20 Refactored JLC Part Numbers. And replaced 100uF capacitors with 1206 sized parts.
2021-02-22 Added second case variant without extruded profiles.
2021-02-23 Added Reset Button to Pi Pico to make updating firmware easier.
2021-02-23 Optimized case model and added supporting parts like Nuts, bolts and screws.
2021-02-23 Cleaned up
2021-03-07 Recreated some parts
2021-03-13 Updated button caps and frontpanel layout.
2021-03-15 Replaced Side Buttons and E5. Relocated HP Capacitors.
2021-03-16 Rearranged elements and added HDMI Port to right sideplate.
2021-03-16 Made the inner breakout area for the tft smaller.
